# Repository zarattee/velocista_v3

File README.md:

# velocista_v3
 Los robots seguidores de línea son robots muy sencillos, que cumplen una única misión: seguir una línea marcada en el suelo normalmente de color negro sobre un tablero blanco.

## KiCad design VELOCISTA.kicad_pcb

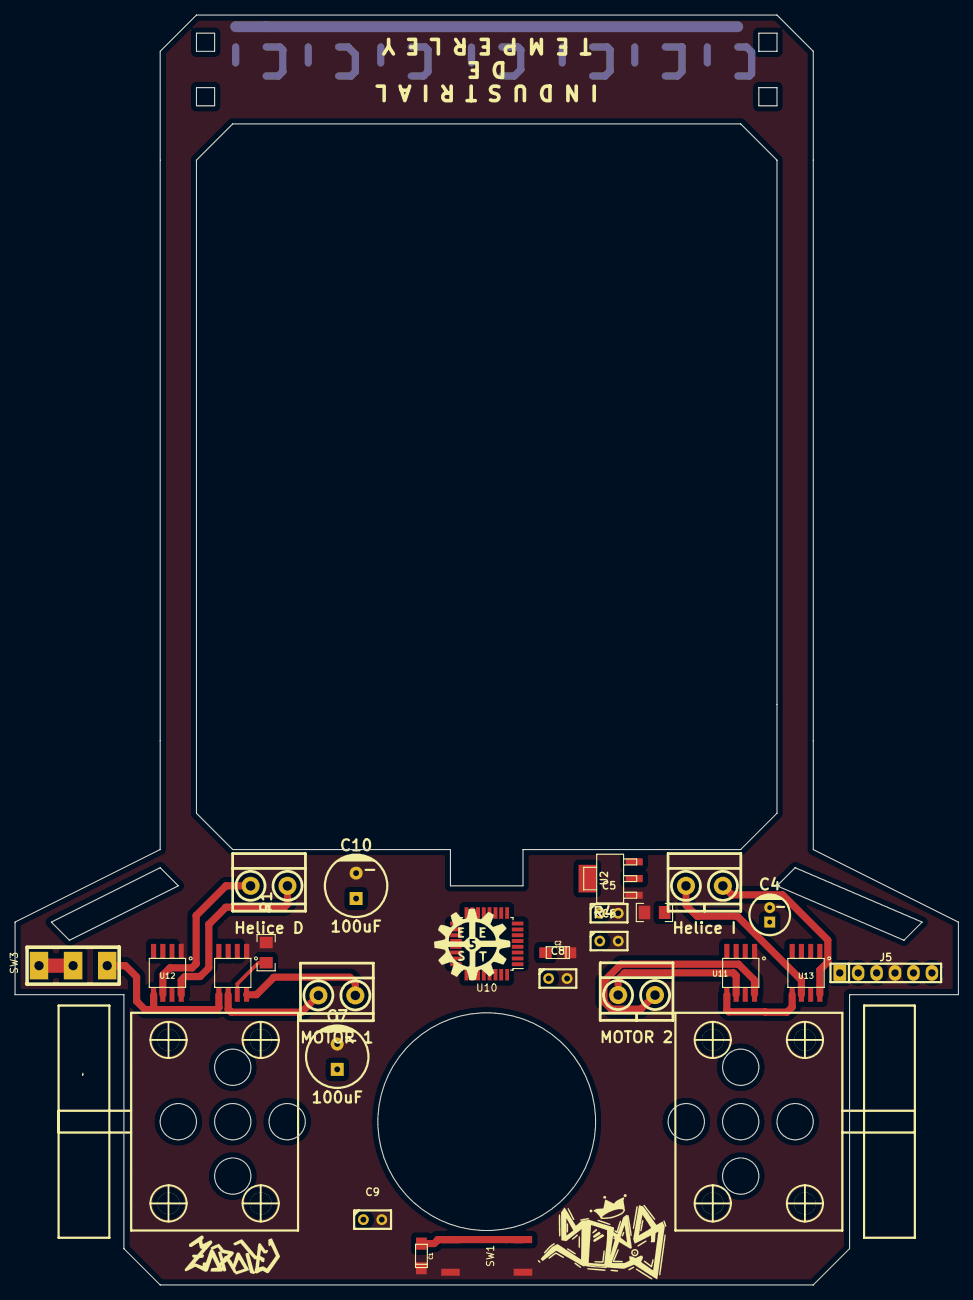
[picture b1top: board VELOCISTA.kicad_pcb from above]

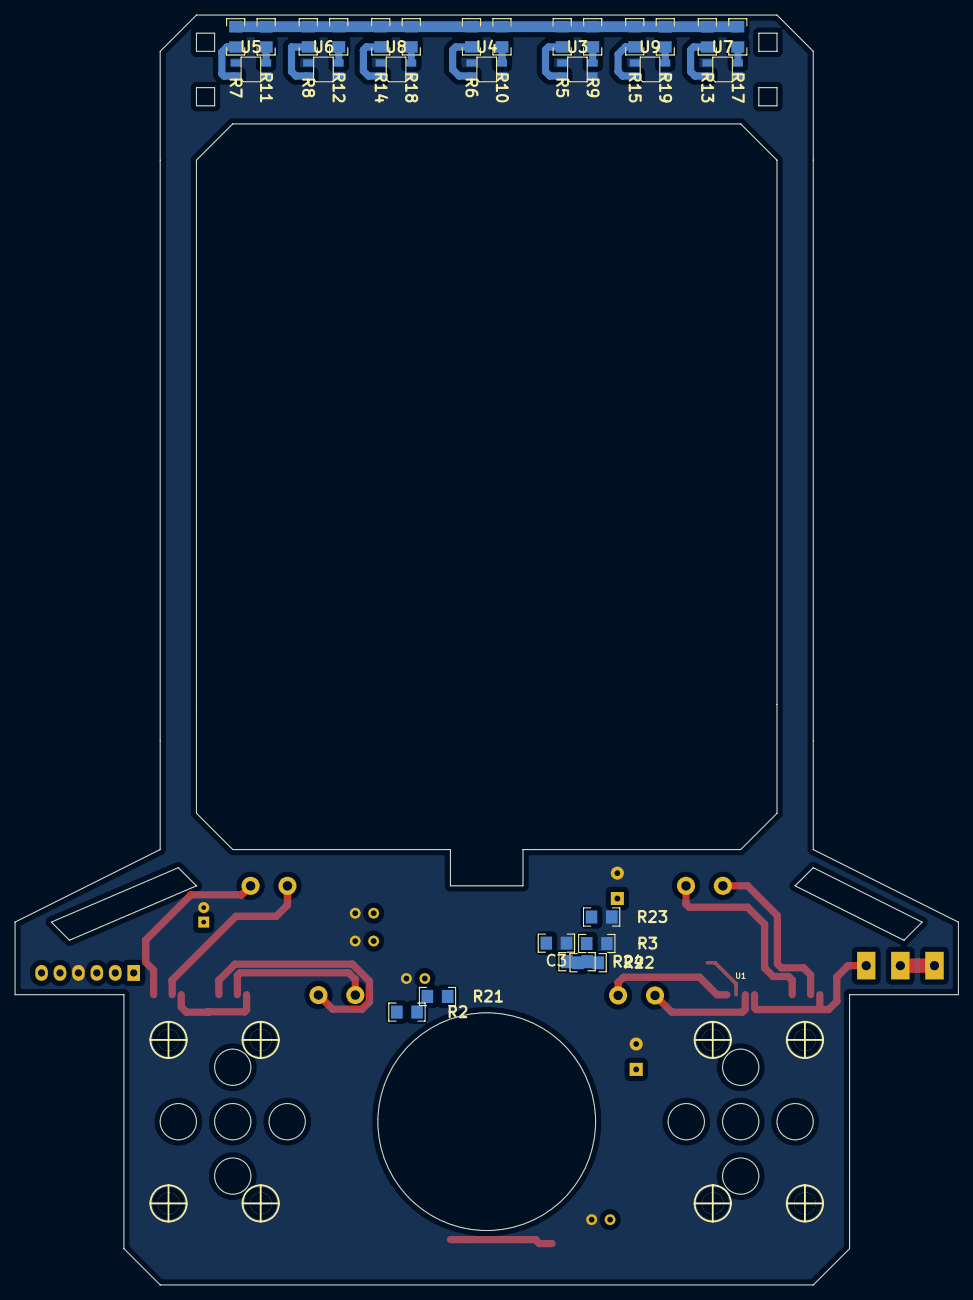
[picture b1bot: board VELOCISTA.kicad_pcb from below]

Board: 2 copper layers, 130.0 x 175.0 mm, 57 parts (28 on the bottom side), 34 nets.

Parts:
C1: 10UF; CAP_TAN_A
C2: 100uF; CAP_TAN_A
C3: 100nF; C_1206
C4: 100uF; CAP_ELEC_5x11mm
C5, C6, C8, C9: 100nF; CAP_0.1
C7, C10: 100uF; CAP_ELEC_8x11.5mm
J3: MOTOR 1; BORNERA2_AZUL
J4: MOTOR 2; BORNERA2_AZUL
J5: HC-05; pin_strip_6
J6: Helice D; BORNERA2_AZUL
J7: Helice I; BORNERA2_AZUL
LG1: Mounting_Hole; LOGO_EESTN5
LG2: Mounting_Hole; Logo_Zarate
LG3: Mounting_Hole; Logo_Zarate_Nombre
R1, R4: Rsense; R_1206
R2: 10K; R_1206
R3, R24: 0.25; R_1206
R5, R6, R7, R8, R13, R14, R15: 220; R_1206
R9, R10, R11, R12, R17, R18, R19: 1OK; R_1206
R21, R22, R23: 1k; R_1206
RD1: Mounting_Hole; Pololu_Micro_Gear_Motor_W_Mount
RI1: Mounting_Hole; Pololu_Micro_Gear_Motor_W_Mount
SW1: SW_PUSH; Pulsador_4_SMD
SW3: SW_SPDT; SW_SPDT_TH_Vertical
U1, U11, U12, U13: DRV8872; SSOP-8
U2: LM1117-SOT; SOT223
U3, U4, U5, U6, U7, U8, U9: QRE1113; QRE1113GR
U10: ATMEGA328P-AU; TQFP-32_7x7mm_Pitch0.8mm

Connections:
+5V: C3.1, C4.1, J5.5, R2.1, R5.1, R6.1, R7.1, R8.1, R9.1, R10.1, R11.1, R12.1, R13.1, R14.1, R15.1, R17.1, R18.1, R19.1, U2.2, U2.4
/A1: R12.2, U6.3
/A2: R19.2, U9.3
/A3: R11.2, U5.3
/A4: R18.2, U8.3
/A5: R10.2, U4.3
/A6: R17.2, U7.3
/A7: R9.2, U3.3
/M1A: J3.1, U1.6
/M1B: J3.2, U1.8
/M2A: J4.1, U11.6
/M2B: J4.2, U11.8
/START: C1.1, R2.2, SW1.3, SW1.4
/VIN: C2.1, C5.1, C6.1, C7.1, C8.1, C9.1, C10.1, SW3.3, U1.5, U2.3, U11.5, U12.5, U13.5
GND: C1.2, C2.2, C3.2, C4.2, C5.2, C6.2, C7.2, C8.2, C9.2, C10.2, J5.4, R1.2, R3.2, R4.2, R23.2, R24.2, SW1.1, SW1.2, U1.1, U2.1, U3.2, U3.4, U4.2, U4.4, U5.2, U5.4, U6.2, U6.4, U7.2, U7.4, U8.2, U8.4, U9.2, U9.4, U11.1, U12.1, U13.1
unnamed: SW3.1, SW3.2
unnamed: J5.2, R21.2, R22.1
unnamed: J6.1, U12.6
unnamed: J6.2, U12.8
unnamed: J7.1, U13.6
unnamed: J7.2, U13.8
unnamed: R1.1, U1.7
unnamed: R3.1, U11.7
unnamed: R4.1, U12.7
unnamed: R5.2, U3.1
unnamed: R6.2, U4.1
unnamed: R7.2, U5.1
unnamed: R8.2, U6.1
unnamed: R13.2, U7.1
unnamed: R14.2, U8.1
unnamed: R15.2, U9.1
unnamed: R22.2, R23.1
unnamed: R24.1, U13.7
unnamed: U10.3, U10.5, U10.21

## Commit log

2020-11-02 robot seguidor de linea en desarrollo
    placa de robot seguidor de linea
    version 3, placa para uso profesonal
